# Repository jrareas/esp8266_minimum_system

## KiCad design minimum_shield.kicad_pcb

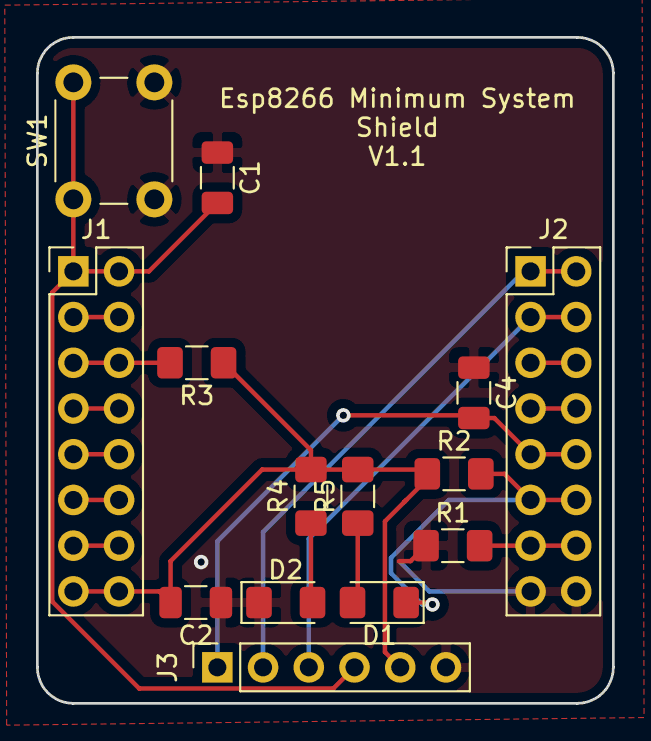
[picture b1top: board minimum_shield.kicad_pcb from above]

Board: 2 copper layers, 32.0 x 37.0 mm, 14 parts (0 on the bottom side), 18 nets.

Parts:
C1, C2, C4: 100nf; C_1206_3216Metric
D1: GREEN; LED_1206_3216Metric_Pad1.42x1.75mm_HandSolder
D2: RED; LED_1206_3216Metric_Pad1.42x1.75mm_HandSolder
J1, J2: Conn_02x08_Odd_Even; PinHeader_2x08_P2.54mm_Vertical
J3: Conn_01x06; PinSocket_1x06_P2.54mm_Vertical
R1: 10k; R_1206_3216Metric_Pad1.42x1.75mm_HandSolder
R2, R3: 5k1; R_1206_3216Metric_Pad1.42x1.75mm_HandSolder
R4, R5: 220; R_1206_3216Metric_Pad1.42x1.75mm_HandSolder
SW1: SW_Push; SW_PUSH_6mm

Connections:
ADC: J1.3, J1.4
EN: J1.5, J1.6, R3.2
GND: C1.1, C2.1, C4.1, D2.1, J2.15, J2.16, J3.6, R1.1, SW1.2
IO0: C4.2, J2.9, J2.10, J3.1
IO2: D1.1, J2.11, J2.12, R2.2
IO4: J2.7, J2.8
IO5: J2.5, J2.6
IO12: J1.11, J1.12
IO13: J1.13, J1.14
IO14: J1.9, J1.10
IO15: J2.13, J2.14, R1.2
IO16: J1.7, J1.8
unnamed: D1.2, R5.1
unnamed: D2.2, R4.1
RST: C1.2, J1.1, J1.2, J3.4, SW1.1
RX: J2.3, J2.4, J3.3
TX: J2.1, J2.2, J3.2
VCC: C2.2, J1.15, J1.16, J3.5, R2.1, R3.1, R4.2, R5.2

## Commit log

2020-12-23 Version 1.0
2021-01-05 V1.1 - fixing missing ground connection to pull up resistor for GPIO15
2021-01-10 ignoring some files
